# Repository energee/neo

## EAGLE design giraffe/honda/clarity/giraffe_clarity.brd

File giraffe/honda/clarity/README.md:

Honda Clarity Giraffe
====

Get your panda deeper into your Clarity

The switches
====

The 4 DIP switches control signals to the stock ADAS system

- 1 -- ADAS F-CAN_A -> panda CAN1

- 2 -- ADAS RADAR-CAN -> panda CAN2 (OBDII pins 12 & 13)

- 3 -- ADAS F-CAN_B -> panda CAN3

- 4 -- ADAS power & ignition -> power & ignition

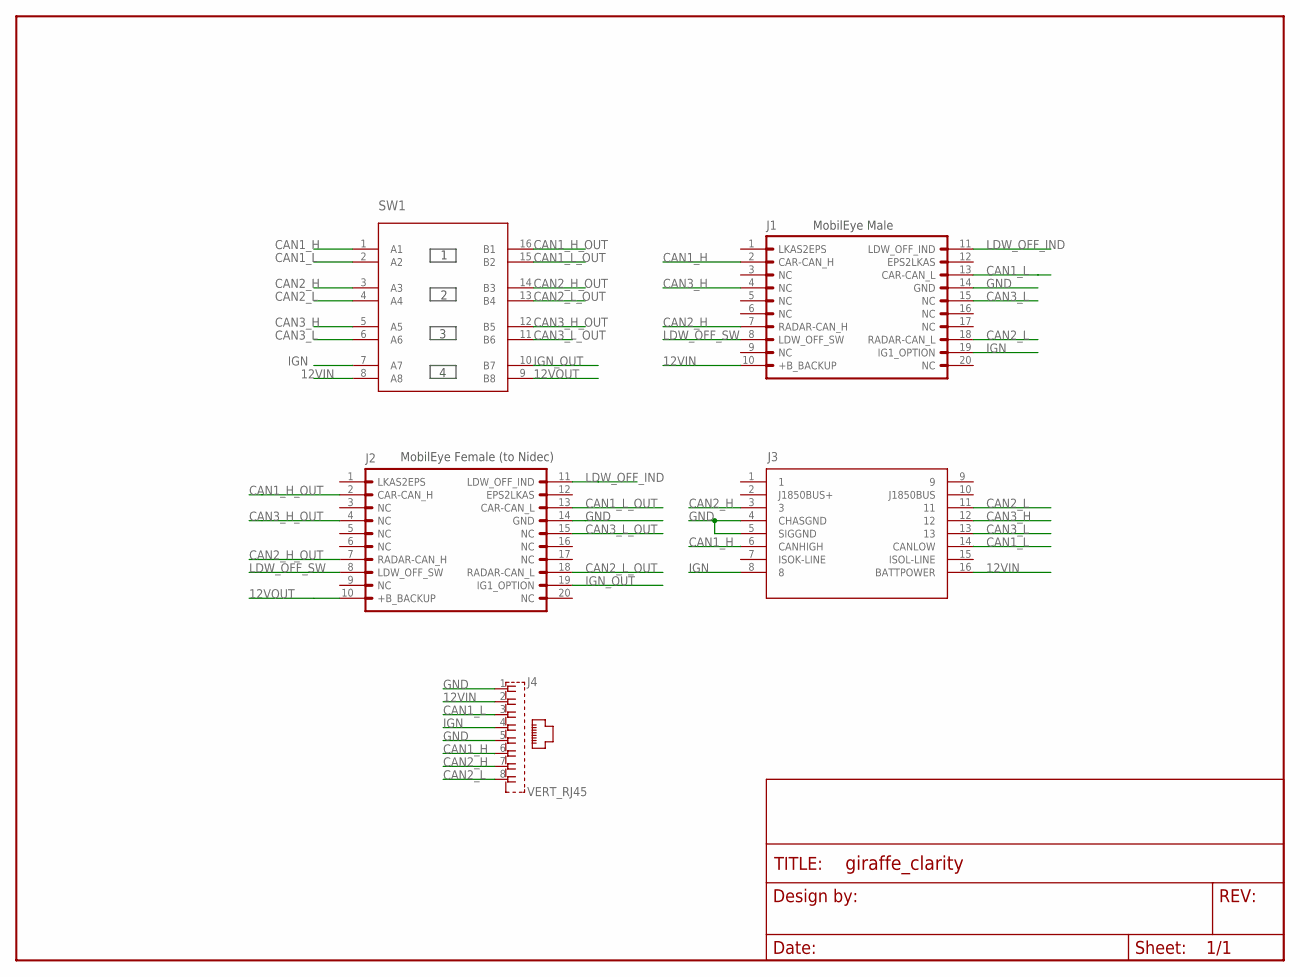
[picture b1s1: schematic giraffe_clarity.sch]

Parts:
FRAME1: FRAME-LETTERNO_PACKAGE; DUMMY
J1: MOBILEYERAMALE; 2X10(RA)
J2: MOBILEYEFEMALE; 2X10(JAE_FEMALE)
J3: OBDII-FEMALE-CUT; OBDII-FEMALE-MIDCUT
J4: VERT_RJ45; GLX-S-88M
SW1: 4XDPSTSMT; 4-DPST

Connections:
12VIN: J1.10 (+B_BACKUP), J3.16 (BATTPOWER), J4.2, SW1.8 (A8)
12VOUT: J2.10 (+B_BACKUP), SW1.9 (B8)
CAN1_H: J1.2 (CAR-CAN_H), J3.6 (CANHIGH), J4.6, SW1.1 (A1)
CAN1_H_OUT: J2.2 (CAR-CAN_H), SW1.16 (B1)
CAN1_L: J1.13 (CAR-CAN_L), J3.14 (CANLOW), J4.3, SW1.2 (A2)
CAN1_L_OUT: J2.13 (CAR-CAN_L), SW1.15 (B2)
CAN2_H: J1.7 (RADAR-CAN_H), J3.3, J4.7, SW1.3 (A3)
CAN2_H_OUT: J2.7 (RADAR-CAN_H), SW1.14 (B3)
CAN2_L: J1.18 (RADAR-CAN_L), J3.11, J4.8, SW1.4 (A4)
CAN2_L_OUT: J2.18 (RADAR-CAN_L), SW1.13 (B4)
CAN3_H: J1.4 (NC), J3.12, SW1.5 (A5)
CAN3_H_OUT: J2.4 (NC), SW1.12 (B5)
CAN3_L: J1.15 (NC), J3.13, SW1.6 (A6)
CAN3_L_OUT: J2.15 (NC), SW1.11 (B6)
GND: J1.14 (GND), J2.14 (GND), J3.4 (CHASGND), J3.5 (SIGGND), J4.1, J4.5
IGN: J1.19 (IG1_OPTION), J3.8, J4.4, SW1.7 (A7)
IGN_OUT: J2.19 (IG1_OPTION), SW1.10 (B7)
LDW_OFF_IND: J1.11 (LDW_OFF_IND), J2.11 (LDW_OFF_IND)
LDW_OFF_SW: J1.8 (LDW_OFF_SW), J2.8 (LDW_OFF_SW)

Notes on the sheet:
MobilEye Male
MobilEye Female (to Nidec)

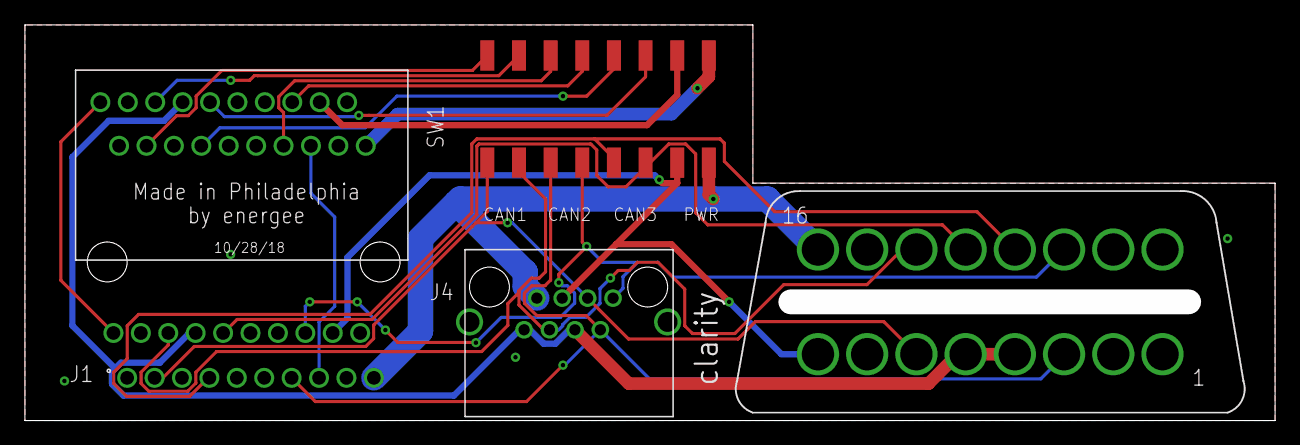
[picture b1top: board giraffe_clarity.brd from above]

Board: 2 copper layers, 100.3 x 31.8 mm, 6 parts (1 on the bottom side), 19 nets.

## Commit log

2017-11-29 added honda bosch giraffe
2018-10-26 Add Odyssey giraffe
2018-10-28 Add Clarity board
2018-10-28 Update flipped board
2018-10-28 Remove inverted giraffe and add clarity docs
2018-10-28 Added minor tweaks
2018-10-28 Moved silkscreens
2018-10-28 Fixed ground vias
2018-10-30 Updated both board traces

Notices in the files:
parts and their libraries:
SparkFun-Aesthetics: Licensing: Creative Commons ShareAlike 4.0 International - https://creativecommons.org/licenses/by-sa/4.0
SparkFun-Aesthetics: Released under the Creative Commons Attribution Share-Alike 4.0 License
SparkFun-Aesthetics: https://creativecommons.org/licenses/by-sa/4.0
